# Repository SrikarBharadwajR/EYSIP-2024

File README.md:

# EYSIP-2024
Repository of EYSIP-2024, Project Name: IEC-Compliant PCB Design and Embedded Systems Development

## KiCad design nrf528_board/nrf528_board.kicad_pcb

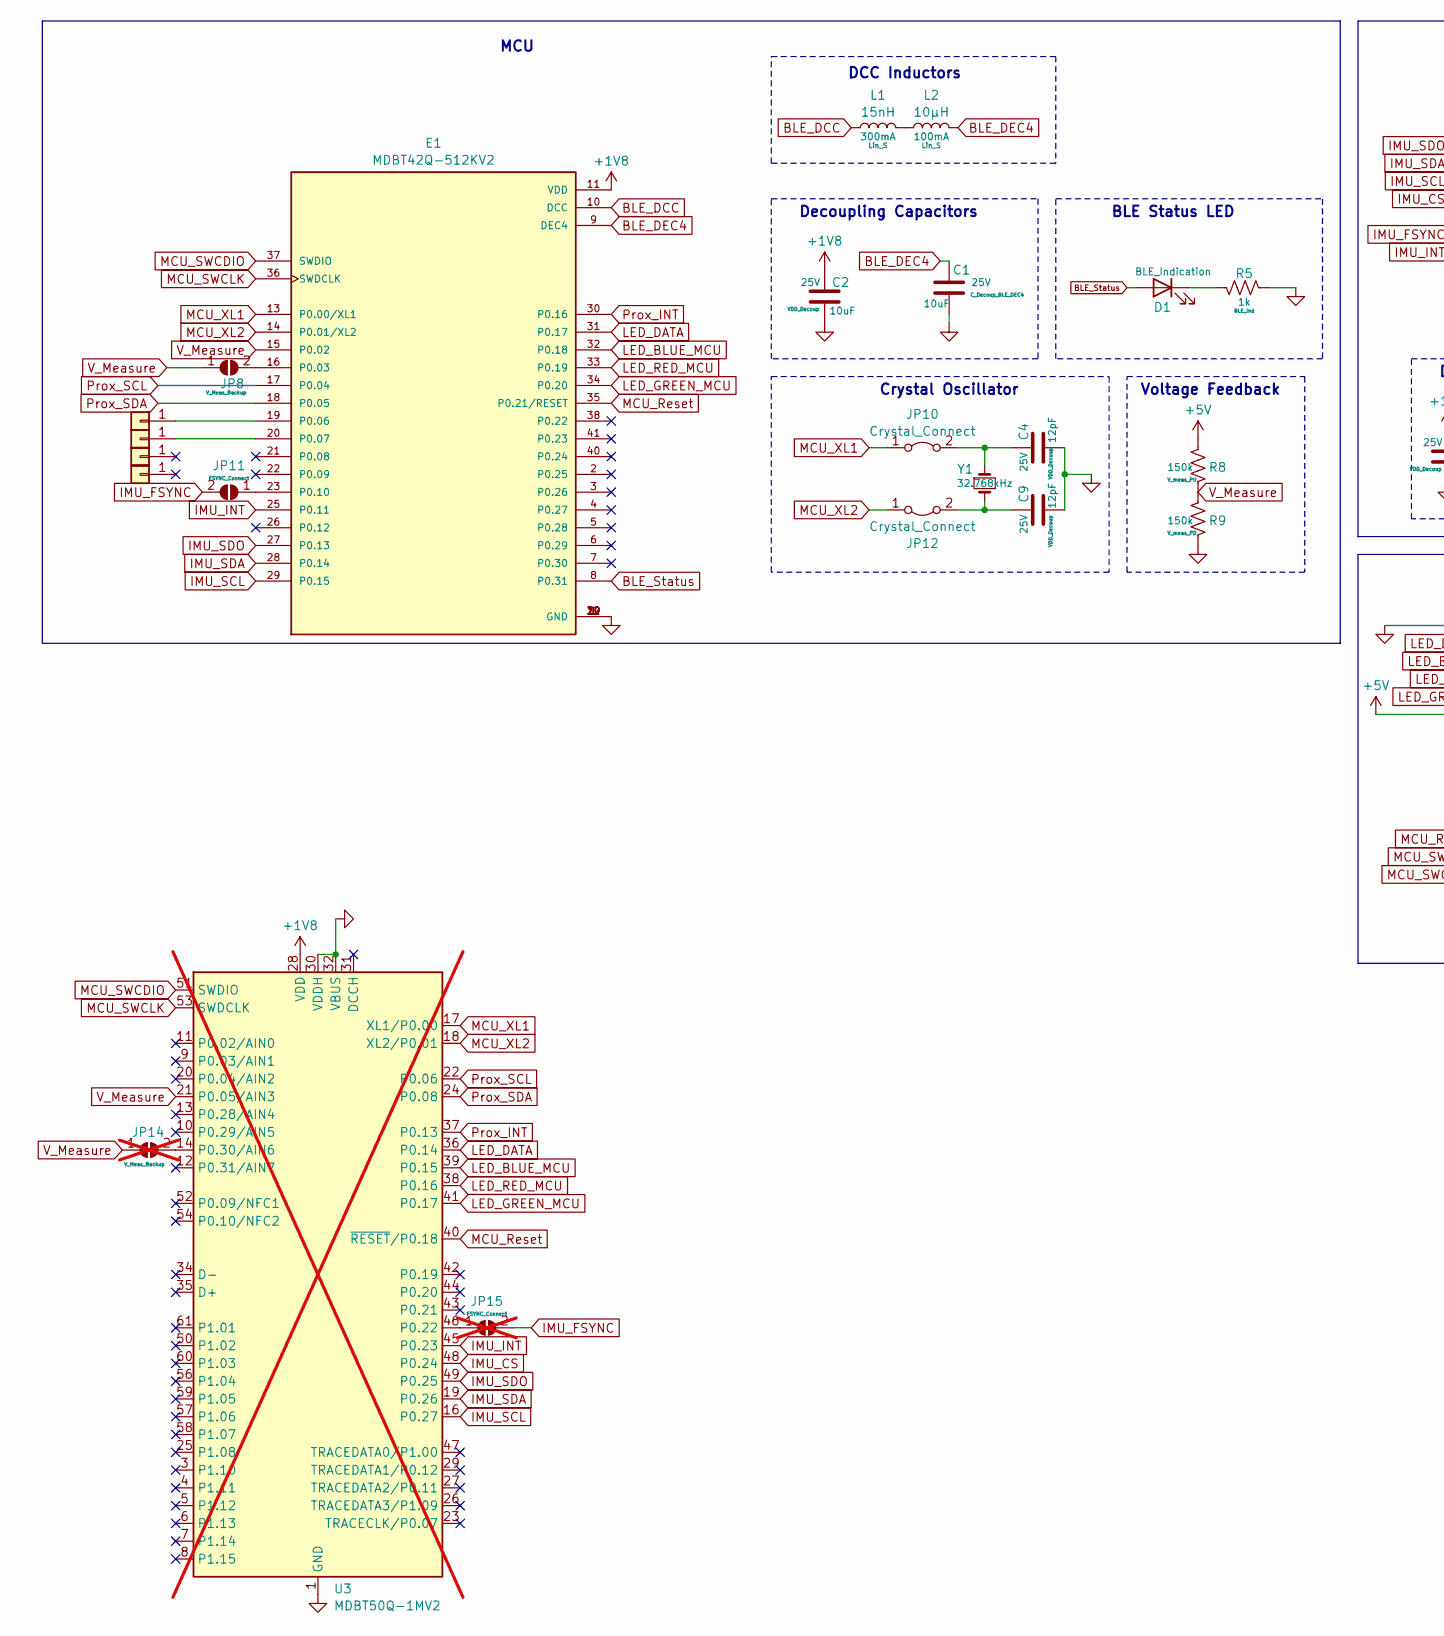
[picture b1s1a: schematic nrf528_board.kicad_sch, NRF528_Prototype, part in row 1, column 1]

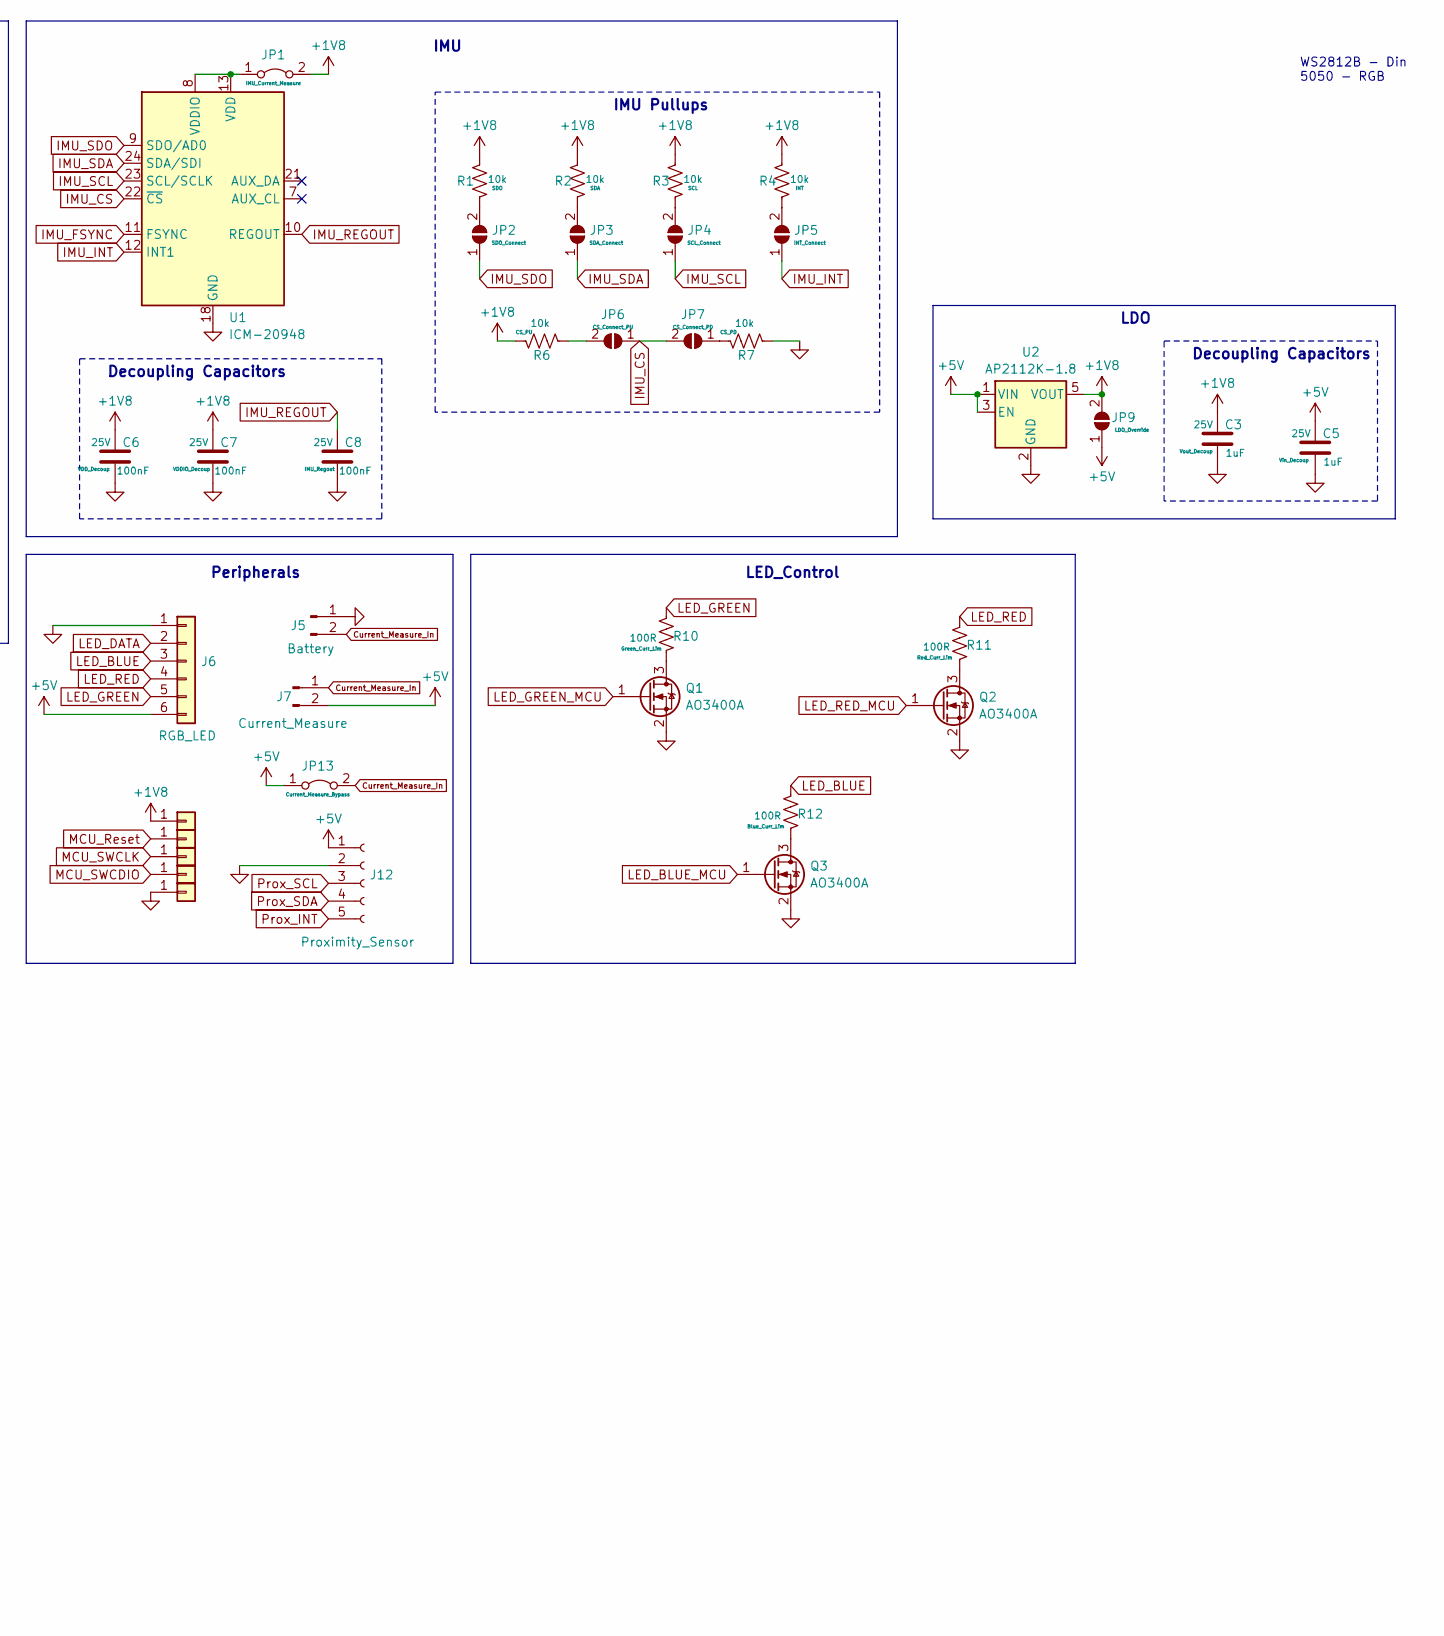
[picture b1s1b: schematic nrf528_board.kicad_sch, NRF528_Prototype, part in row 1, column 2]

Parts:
C1, C2: 10uF; C_0805_2012Metric_Pad1.18x1.45mm_HandSolder; Voltage 25V
C3, C5: 1uF; C_0805_2012Metric_Pad1.18x1.45mm_HandSolder; Voltage 25V
C4, C9: 12pF; C_0805_2012Metric_Pad1.18x1.45mm_HandSolder; Voltage 25V
C6, C7, C8: 100nF; C_0805_2012Metric_Pad1.18x1.45mm_HandSolder; Voltage 25V
D1: BLE_Indication; LED_0805_2012Metric_Pad1.15x1.40mm_HandSolder
E1: MDBT42Q-512KV2; RAYTAC_MDBT42Q-512KV2; PARTREV J
J1, J2, J8, J9, J10, J11, J13: Conn_01x01; TestPoint_Pad_D1.5mm
J3, J4: Conn_01x01
J5: Battery; PinHeader_1x02_P2.54mm_Vertical
J6: RGB_LED; PinSocket_1x06_P2.54mm_Vertical
J7: Current_Measure; PinHeader_1x02_P2.54mm_Vertical
J12: Proximity_Sensor; PinSocket_1x05_P2.54mm_Vertical
JP1: IMU_Current_Measure; SolderJumper-2_P1.3mm_Open_RoundedPad1.0x1.5mm
JP2: SDO_Connect; SolderJumper-2_P1.3mm_Open_RoundedPad1.0x1.5mm
JP3: SDA_Connect; SolderJumper-2_P1.3mm_Open_RoundedPad1.0x1.5mm
JP4: SCL_Connect; SolderJumper-2_P1.3mm_Open_RoundedPad1.0x1.5mm
JP5: INT_Connect; SolderJumper-2_P1.3mm_Open_RoundedPad1.0x1.5mm
JP6: CS_Connect_PU; SolderJumper-2_P1.3mm_Open_RoundedPad1.0x1.5mm
JP7: CS_Connect_PD; SolderJumper-2_P1.3mm_Open_RoundedPad1.0x1.5mm
JP8: V_Meas_Backup; SolderJumper-2_P1.3mm_Open_RoundedPad1.0x1.5mm
JP9: LDO_Override; SolderJumper-2_P1.3mm_Open_RoundedPad1.0x1.5mm
JP10, JP12: Crystal_Connect; SolderJumper-2_P1.3mm_Open_RoundedPad1.0x1.5mm
JP11: FSYNC_Connect; SolderJumper-2_P1.3mm_Open_RoundedPad1.0x1.5mm
JP13: Current_Measure_Bypass; SolderJumper-2_P1.3mm_Open_RoundedPad1.0x1.5mm
JP14: V_Meas_Backup; SolderJumper-2_P1.3mm_Open_RoundedPad1.0x1.5mm; not fitted
JP15: FSYNC_Connect; SolderJumper-2_P1.3mm_Open_RoundedPad1.0x1.5mm; not fitted
L1: 15nH; L_0805_2012Metric_Pad1.15x1.40mm_HandSolder
L2: 10μH; L_0805_2012Metric_Pad1.15x1.40mm_HandSolder
Q1, Q2, Q3: AO3400A; SOT-23
R1, R2, R3, R4, R6, R7: 10k; R_0805_2012Metric_Pad1.20x1.40mm_HandSolder
R5: 1k; R_0805_2012Metric_Pad1.20x1.40mm_HandSolder
R8, R9: 150k; R_0805_2012Metric_Pad1.20x1.40mm_HandSolder
R10, R11, R12: 100R; R_0805_2012Metric_Pad1.20x1.40mm_HandSolder
U1: ICM-20948; InvenSense_QFN-24_3x3mm_P0.4mm
U2: AP2112K-1.8; SOT-23-5
U3: MDBT50Q-1MV2; Raytac_MDBT50Q; not fitted
Y1: 32.768kHz; Crystal_SMD_EuroQuartz_EQ161-2Pin_3.2x1.5mm_HandSoldering

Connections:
+1V8: C2.2, C3.2, C6.2, C7.2, E1.11 (VDD), J8.1, JP1.2 (B), JP9.2 (B), R1.2, R2.2, R3.2, R4.2, R6.2, U2.5 (VOUT), U3.28 (VDD)
+5V: C5.2, J6.6, J7.2, J12.1, JP9.1 (A), JP13.1 (A), R8.1, U2.1 (VIN), U2.3 (EN)
BLE_DCC: E1.10 (DCC), L1.1
BLE_DEC4: C1.2, E1.9 (DEC4), L2.2
BLE_Status: D1.2 (A), E1.8 (P0.31)
Current_Measure_In: J5.2, J7.1, JP13.2 (B)
GND: C1.1, C2.1, C3.1, C4.1, C5.1, C6.1, C7.1, C8.1, C9.1, E1.1 (GND), E1.12 (GND), E1.24 (GND), E1.39 (GND), J5.1, J6.1, J12.2, J13.1, Q1.2 (S), Q2.2 (S), Q3.2 (S), R5.2, R7.1, R9.2, U1.18 (GND), U1.20 (GND), U2.2 (GND), U3.1 (GND), U3.2 (GND), U3.15 (GND), U3.30 (VDDH), U3.32 (VBUS), U3.33 (GND), U3.55 (GND)
IMU_CS: JP6.1 (A), JP7.2 (B), U1.22 (~CS), U3.48 (P0.24)
IMU_FSYNC: JP11.2 (B), JP15.2 (B), U1.11 (FSYNC)
IMU_INT: E1.25 (P0.11), JP5.1 (A), U1.12 (INT1), U3.45 (P0.23)
IMU_REGOUT: C8.2, U1.10 (REGOUT)
IMU_SCL: E1.29 (P0.15), JP4.1 (A), U1.23 (SCL/SCLK), U3.16 (P0.27)
IMU_SDA: E1.28 (P0.14), JP3.1 (A), U1.24 (SDA/SDI), U3.19 (P0.26)
IMU_SDO: E1.27 (P0.13), JP2.1 (A), U1.9 (SDO/AD0), U3.49 (P0.25)
LED_BLUE: J6.3, R12.1
LED_BLUE_MCU: E1.32 (P0.18), Q3.1 (G), U3.39 (P0.15)
LED_DATA: E1.31 (P0.17), J6.2, U3.36 (P0.14)
LED_GREEN: J6.5, R10.1
LED_GREEN_MCU: E1.34 (P0.20), Q1.1 (G), U3.41 (P0.17)
LED_RED: J6.4, R11.1
LED_RED_MCU: E1.33 (P0.19), Q2.1 (G), U3.38 (P0.16)
MCU_Reset: E1.35 (P0.21/RESET), J9.1, U3.40 (~RESET/P0.18)
MCU_SWCDIO: E1.37 (SWDIO), J11.1, U3.51 (SWDIO)
MCU_SWCLK: E1.36 (SWDCLK), J10.1, U3.53 (SWDCLK)
MCU_XL1: E1.13 (P0.00/XL1), JP10.1 (A), U3.17 (XL1/P0.00)
MCU_XL2: E1.14 (P0.01/XL2), JP12.1 (A), U3.18 (XL2/P0.01)
unnamed: D1.1 (K), R5.1
unnamed: E1.16 (P0.03), JP8.2 (B)
unnamed: E1.19 (P0.06), J1.1
unnamed: E1.20 (P0.07), J2.1
unnamed: E1.23 (P0.10), JP11.1 (A)
unnamed: JP1.1 (A), U1.8 (VDDIO), U1.13 (VDD)
unnamed: JP2.2 (B), R1.1
unnamed: JP3.2 (B), R2.1
unnamed: JP4.2 (B), R3.1
unnamed: JP5.2 (B), R4.1
unnamed: JP6.2 (B), R6.1
unnamed: JP7.1 (A), R7.2
unnamed: C4.2, JP10.2 (B), Y1.1
unnamed: C9.2, JP12.2 (B), Y1.2
unnamed: JP14.2 (B), U3.14 (P0.30/AIN6)
unnamed: JP15.1 (A), U3.46 (P0.22)
unnamed: L1.2, L2.1
unnamed: Q1.3 (D), R10.2
unnamed: Q2.3 (D), R11.2
unnamed: Q3.3 (D), R12.2
Prox_INT: E1.30 (P0.16), J12.5, U3.37 (P0.13)
Prox_SCL: E1.17 (P0.04), J12.3, U3.22 (P0.06)
Prox_SDA: E1.18 (P0.05), J12.4, U3.24 (P0.08)
V_Measure: E1.15 (P0.02), JP8.1 (A), JP14.1 (A), R8.2, R9.1, U3.21 (P0.05/AIN3)

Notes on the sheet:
Decoupling Capacitors
Crystal Oscillator
BLE Status LED
DCC Inductors
WS2812B - Din 5050 - RGB
LED_Control
MCU
LDO
IMU
IMU Pullups
Peripherals
Voltage Feedback

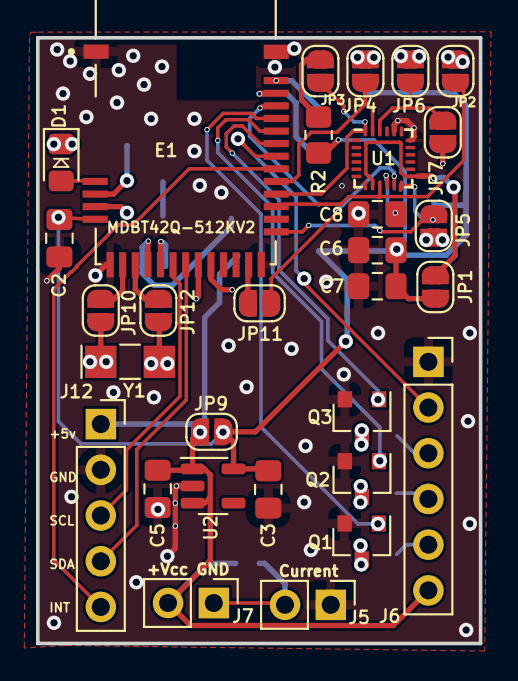
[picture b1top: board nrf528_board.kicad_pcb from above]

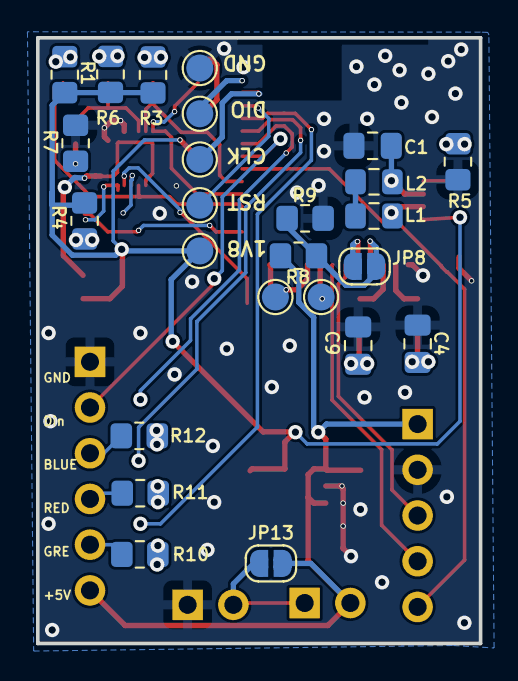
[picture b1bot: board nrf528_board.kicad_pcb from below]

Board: 2 copper layers, 24.6 x 33.6 mm, 55 parts (25 on the bottom side), 48 nets.

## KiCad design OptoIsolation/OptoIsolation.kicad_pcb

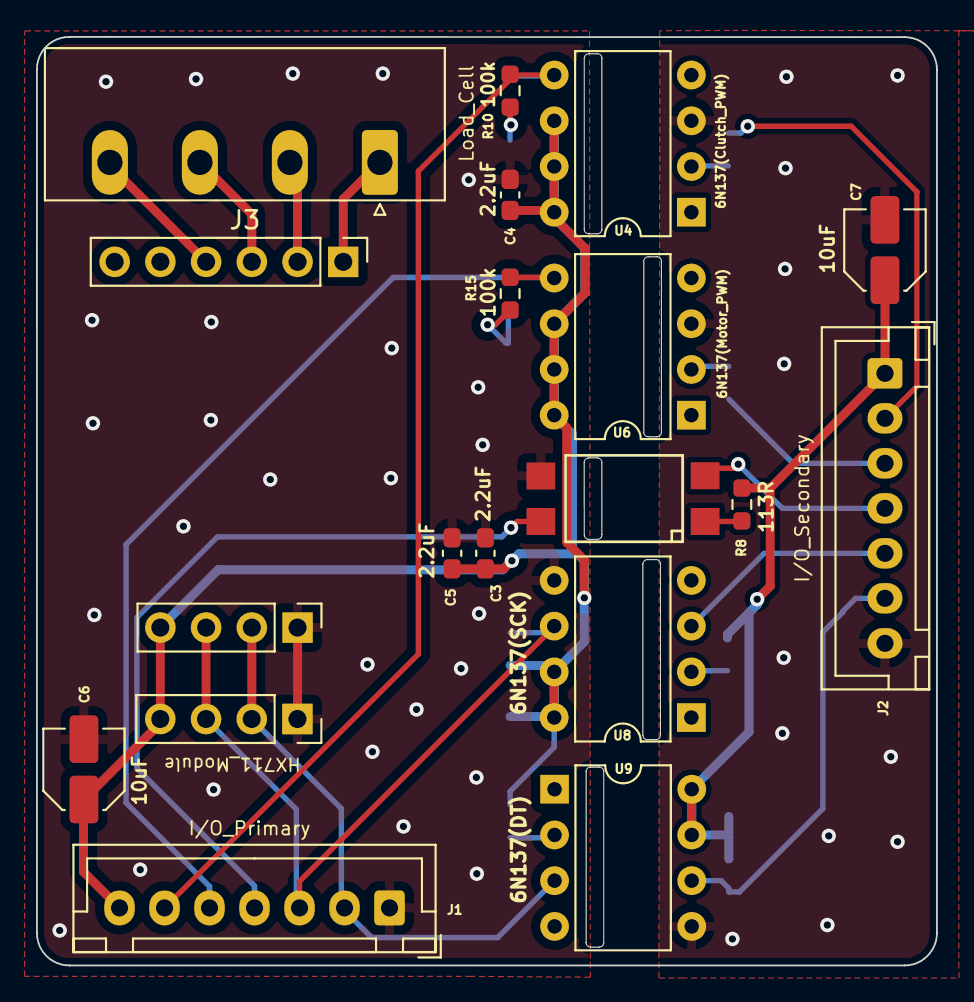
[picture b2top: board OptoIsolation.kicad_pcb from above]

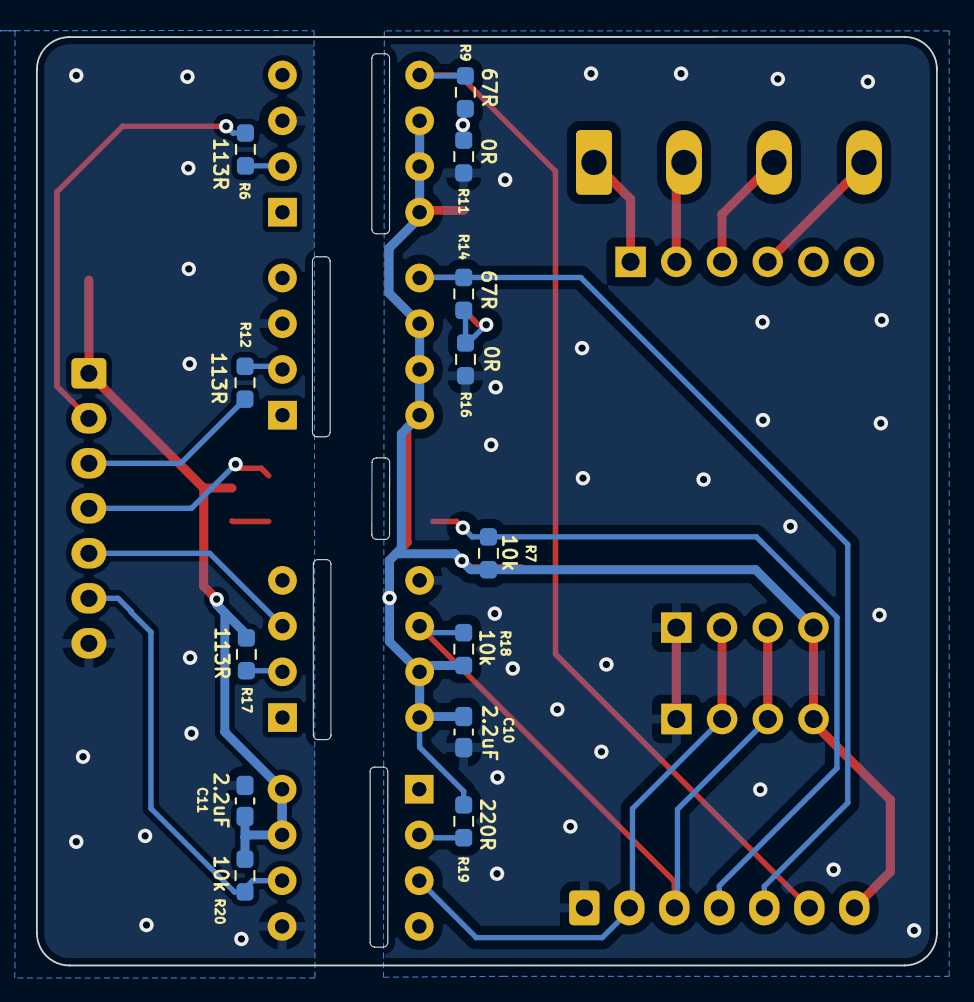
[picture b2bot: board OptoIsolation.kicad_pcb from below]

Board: 2 copper layers, 50.0 x 51.6 mm, 31 parts (13 on the bottom side), 25 nets.

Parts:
C3, C4, C5, C10, C11: 2.2uF; C_0603_1608Metric_Pad1.08x0.95mm_HandSolder
C6, C7: 10uF; C_Elec_4x5.4
J1: I/O_Primary; JST_XH_B7B-XH-A_1x07_P2.50mm_Vertical
J2: I/O_Secondary; JST_XH_B7B-XH-A_1x07_P2.50mm_Vertical
J3: Load_Cell; PhoenixContact_MSTBA_2,5_4-G_1x04_P5.00mm_Horizontal
J4: Old_HX-711_Connector; PinSocket_1x04_P2.54mm_Vertical
R6, R8, R12, R17: 113R; R_0603_1608Metric_Pad0.98x0.95mm_HandSolder
R7, R18, R20: 10k; R_0603_1608Metric_Pad0.98x0.95mm_HandSolder
R9, R14: 67R; R_0603_1608Metric_Pad0.98x0.95mm_HandSolder
R10, R15: 100k; R_0603_1608Metric_Pad0.98x0.95mm_HandSolder
R11, R16: 0R; R_0603_1608Metric_Pad0.98x0.95mm_HandSolder
R19: 220R; R_0603_1608Metric_Pad0.98x0.95mm_HandSolder
U4: 6N137(Clutch_PWM); DIP-8_W7.62mm
U5: EL817(Motor_Dir); OPTO-SMD4
U6: 6N137(Motor_PWM); DIP-8_W7.62mm
U7: HX711_Module
U8: 6N137(SCK); DIP-8_W7.62mm
U9: 6N137(DT); DIP-8_W7.62mm

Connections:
+3.3VS: C7.1, C11.1, J2.1, R8.1, R17.1, R20.1, U9.7 (VE), U9.8 (VCC)
+5VP: C3.1, C4.1, C5.1, C6.1, C10.1, J1.7, J4.4, R7.2, R18.1, R19.1, U4.6 (VO), U4.7 (VE), U4.8 (VCC), U6.6 (VO), U6.7 (VE), U6.8 (VCC), U7.7 (Vcc), U8.7 (VE), U8.8 (VCC)
Black: J3.2, U7.2 (E-)
Clutch_Input_PWM: J2.2, R6.1
Clutch_Output_PWM: J1.6, R9.2, R10.2, U4.5 (GND)
GNDP: C3.2, C4.2, C5.2, C6.2, C10.2, J1.1, J4.1, R11.2, R16.2, U5.3, U7.10 (GND), U8.5 (GND)
GNDS: C7.2, C11.2, J2.7, U4.3 (K), U6.3 (K), U9.5 (GND)
Green: J3.4, U7.4 (A+)
HX711_DT: J1.2, J4.2, U7.9 (DT), U9.3 (K)
HX711_SCK: J1.3, J4.3, R18.2, U7.8 (SCK), U8.6 (VO)
MCU_DT: J2.6, R20.2, U9.6 (VO)
MCU_SCK: J2.5, U8.3 (K)
Motor_Input_DIR: J2.4, U5.2
Motor_Input_PWM: J2.3, R12.1
Motor_Output_DIR: J1.4, R7.1, U5.4
Motor_Output_PWM: J1.5, R14.2, R15.2, U6.5 (GND)
unnamed: R8.2, U5.1
unnamed: R9.1, R10.1, R11.1
unnamed: R14.1, R15.1, R16.1
unnamed: R6.2, U4.2 (A)
unnamed: R12.2, U6.2 (A)
unnamed: R17.2, U8.2 (A)
unnamed: R19.2, U9.2 (A)
Red: J3.1, U7.1 (E+)
White: J3.3, U7.3 (A-)

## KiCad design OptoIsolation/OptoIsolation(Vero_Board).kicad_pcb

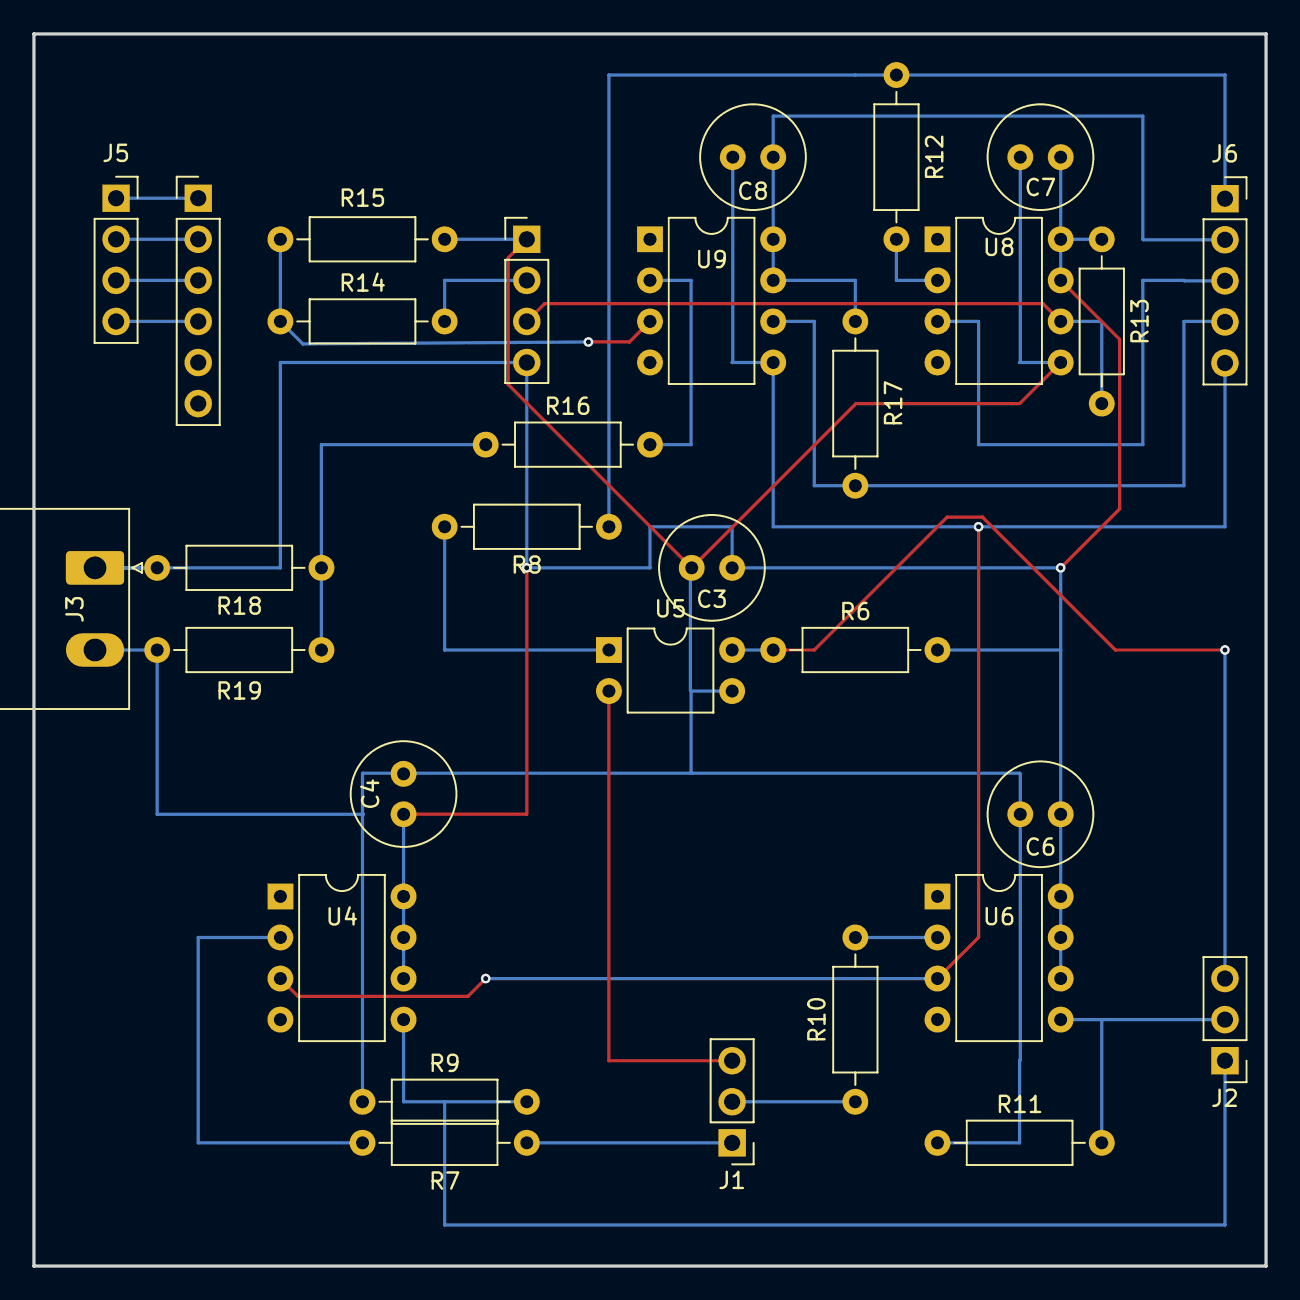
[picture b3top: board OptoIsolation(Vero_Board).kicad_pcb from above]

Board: 2 copper layers, 76.2 x 76.2 mm, 30 parts (0 on the bottom side), 26 nets.

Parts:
C3, C4, C6, C7, C8: 2.2uF; C_Radial_D6.3mm_H5.0mm_P2.50mm
J1: MCU Input; PinHeader_1x03_P2.54mm_Vertical
J2: Driver Output; PinHeader_1x03_P2.54mm_Vertical
J3: Power Socket; PhoenixContact_MSTBA_2,5_2-G-5,08_1x02_P5.08mm_Horizontal
J5: Load Cell Socket; PinSocket_1x04_P2.54mm_Vertical
J6: MCU Connection; PinSocket_1x05_P2.54mm_Vertical
R6, R13, R17: 10k; R_Axial_DIN0207_L6.3mm_D2.5mm_P10.16mm_Horizontal
R7, R8, R10, R12, R16: 130R; R_Axial_DIN0207_L6.3mm_D2.5mm_P10.16mm_Horizontal
R9, R11: 67R; R_Axial_DIN0207_L6.3mm_D2.5mm_P10.16mm_Horizontal
R14, R18: 1k; R_Axial_DIN0207_L6.3mm_D2.5mm_P10.16mm_Horizontal
R15, R19: 2.2k; R_Axial_DIN0207_L6.3mm_D2.5mm_P10.16mm_Horizontal
U4, U6, U8, U9: 6N137; DIP-8_W7.62mm
U5: PC817; DIP-4_W7.62mm
U7: HX711_Module

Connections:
+3.3VP: R16.1, R18.1, R19.2
+3.3VS: J6.1, R8.1, R12.1
+5VP: C3.1, C4.1, C6.1, C7.1, J3.1, R6.2, R13.1, R18.2, U4.6 (VO), U4.7 (VE), U4.8 (VCC), U6.6 (VO), U6.7 (VE), U6.8 (VCC), U7.7 (Vcc), U8.7 (VE), U8.8 (VCC)
+5VS: C8.1, J6.2, R17.1, U9.7 (VE), U9.8 (VCC)
Black: J5.2, U7.2 (E-)
Clutch_Input_PWM: J1.1, R7.1
Clutch_Output_PWM: J2.1, R9.2, U4.5 (GND)
GNDP: C3.2, C4.2, C6.2, C7.2, J3.2, R9.1, R11.1, R15.1, R19.1, U5.3, U7.10 (GND), U8.5 (GND)
GNDS: C8.2, J6.5, U4.3 (K), U6.3 (K), U9.5 (GND)
Green: J5.4, U7.4 (A+)
HX711_DT: R14.1, R15.2, U9.3 (K)
HX711_DT_5V: R14.2, U7.9 (DT)
HX711_SCK: R13.2, U7.8 (SCK), U8.6 (VO)
MCU_DT: J6.4, R17.2, U9.6 (VO)
MCU_SCK: J6.3, U8.3 (K)
Motor_Input_DIR: J1.3, U5.2
Motor_Input_PWM: J1.2, R10.1
Motor_Output_DIR: J2.3, R6.1, U5.4
Motor_Output_PWM: J2.2, R11.2, U6.5 (GND)
unnamed: R8.2, U5.1
unnamed: R7.2, U4.2 (A)
unnamed: R10.2, U6.2 (A)
unnamed: R12.2, U8.2 (A)
unnamed: R16.2, U9.2 (A)
Red: J5.1, U7.1 (E+)
White: J5.3, U7.3 (A-)

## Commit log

2024-07-21 NRF Prototype Board
2024-07-21 OptoIsolation Prototype Board
2024-07-21 HX-711_Interface
2024-07-21 BLE_with_IMU_Main
2024-07-22 Documented Code
